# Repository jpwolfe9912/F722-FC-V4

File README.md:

# F722 Flight Controller V4
[Schematic.pdf](https://github.com/Jpwolfe9912/F722-FC-V4/files/6743878/Schematic.pdf)

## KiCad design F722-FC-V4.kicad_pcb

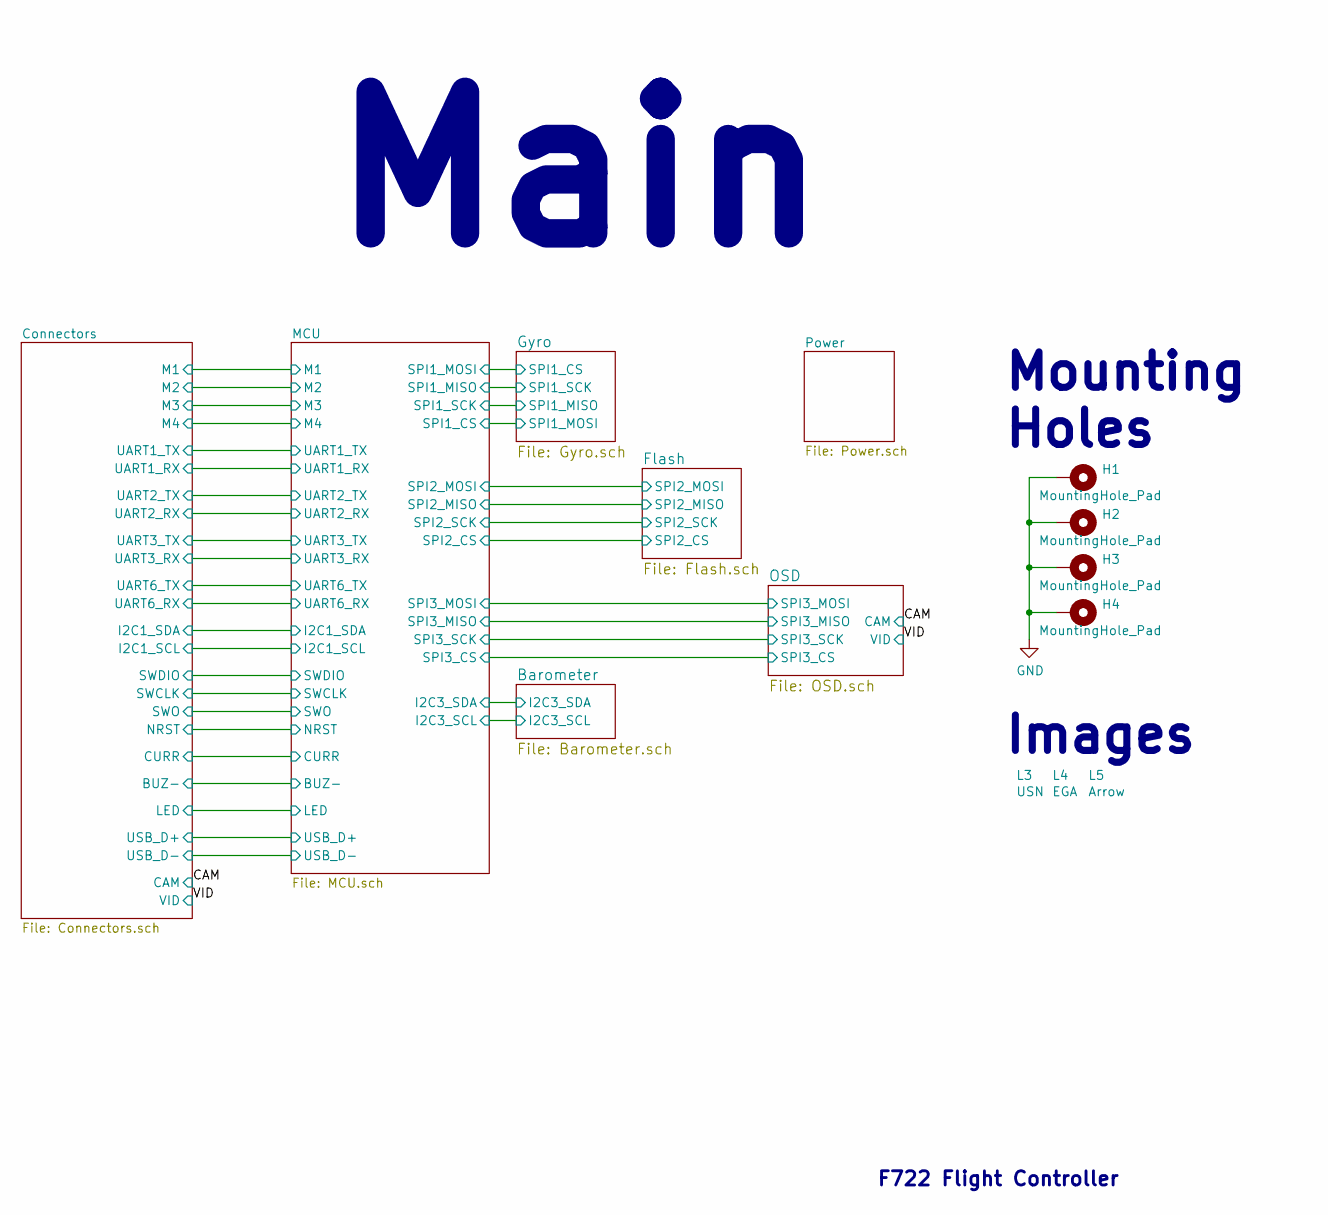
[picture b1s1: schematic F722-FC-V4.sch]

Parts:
H1, H2, H3, H4: MountingHole_Pad; MountingHole_2.7mm_Pad
L3: USN
L4: EGA
L5: Arrow

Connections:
GND: H1.1, H2.1, H3.1, H4.1; also elsewhere on the board

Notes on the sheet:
Mounting Holes
Images
Main
F722 Flight Controller

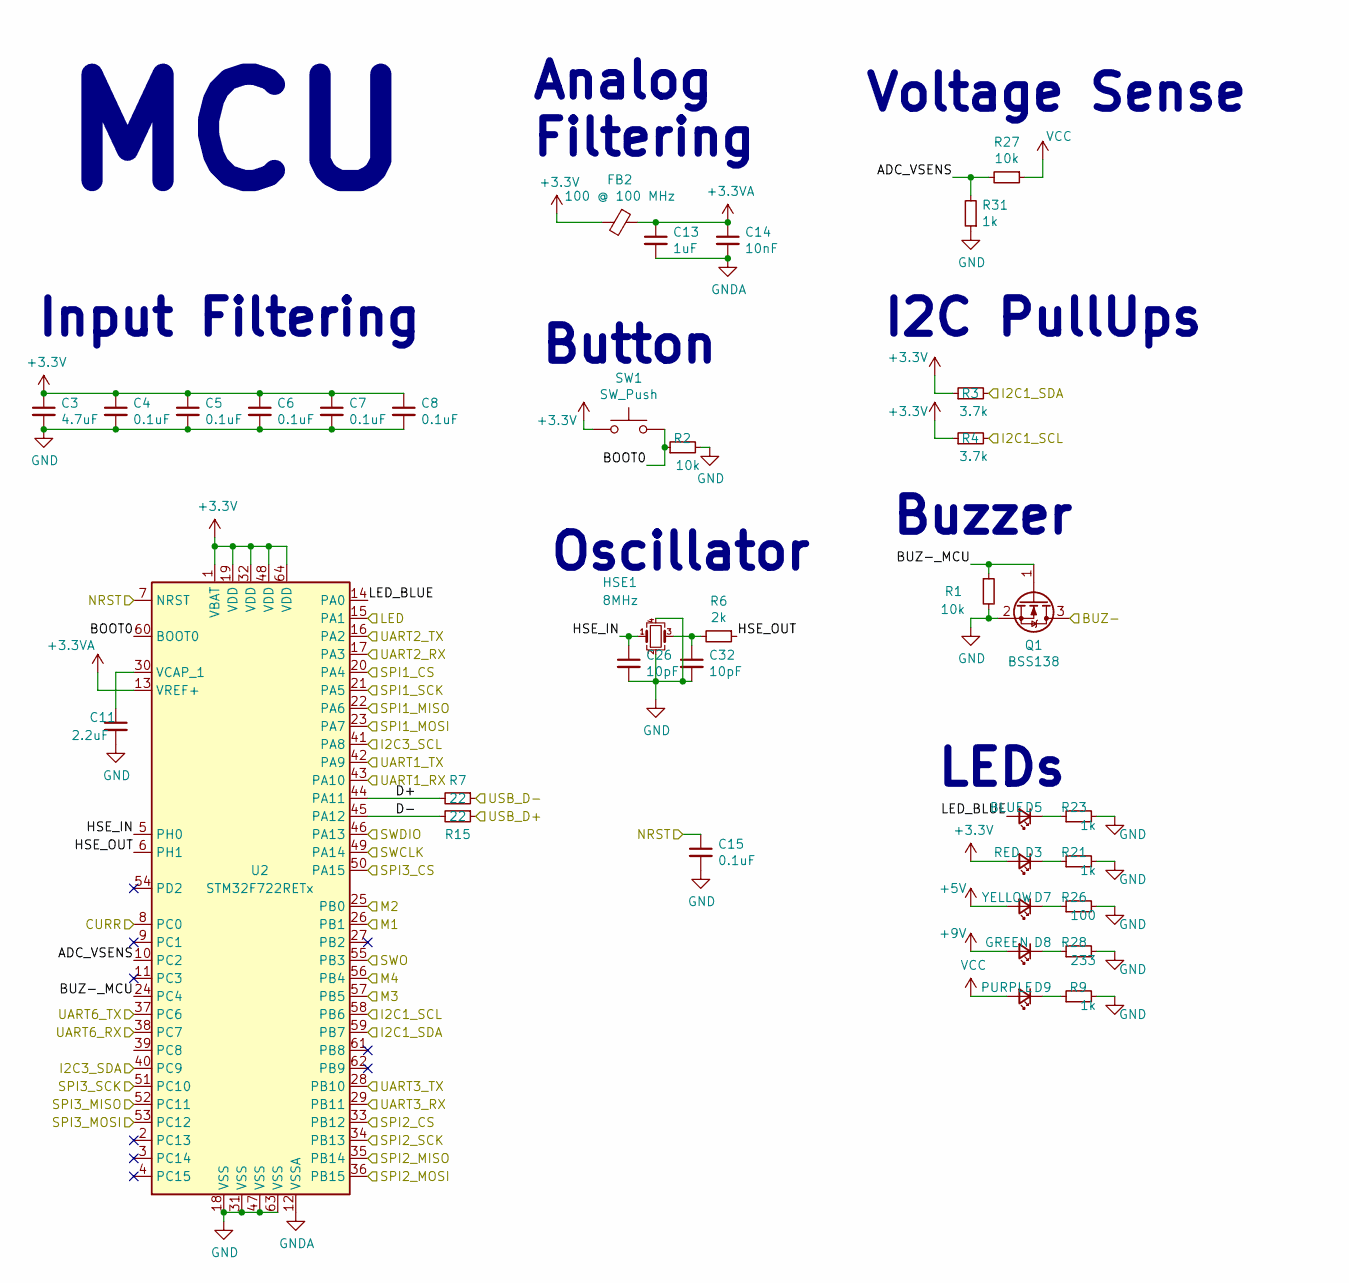
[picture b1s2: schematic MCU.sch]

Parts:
C3: 4.7uF; C_0402_1005Metric
C4, C5, C6, C7, C8, C15: 0.1uF; C_0402_1005Metric
C11: 2.2uF; C_0402_1005Metric
C13: 1uF; C_0402_1005Metric
C14: 10nF; C_0402_1005Metric
C26, C32: 10pF; C_0402_1005Metric
D3: RED; LED_0603_1608Metric
D5: BLUE; LED_0603_1608Metric
D7: YELLOW; LED_0603_1608Metric
D8: GREEN; LED_0603_1608Metric
D9: PURPLE; LED_0603_1608Metric
FB2: 100 @ 100 MHz; L_0603_1608Metric
HSE1: 8MHz; Oscillator_SMD_Abracon_ASE-4Pin_3.2x2.5mm
Q1: BSS138; SOT-23
R1, R2, R27: 10k; R_0402_1005Metric
R3, R4: 3.7k; R_0402_1005Metric
R6: 2k; R_0402_1005Metric
R7, R15: 22; R_0402_1005Metric
R9, R21, R23, R31: 1k; R_0402_1005Metric
R26: 100; R_0402_1005Metric
R28: 233; R_0402_1005Metric
SW1: SW_Push; SW_SPST_B3U-1000P
U2: STM32F722RETx; LQFP-64_10x10mm_P0.5mm

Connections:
+3.3VA: C13.1, C14.1, FB2.1, U2.13 (VREF+)
+5V: D7.2 (A); also elsewhere on the board
+9V: D8.2 (A); also elsewhere on the board
/Barometer/I2C3_SCL: U2.41 (PA8); also elsewhere on the board
/Barometer/I2C3_SDA: U2.40 (PC9); also elsewhere on the board
/Connectors/BUZ-: Q1.3 (D); also elsewhere on the board
/Connectors/CURR: U2.8 (PC0); also elsewhere on the board
/Connectors/I2C1_SCL: R4.2, U2.58 (PB6); also elsewhere on the board
/Connectors/I2C1_SDA: R3.2, U2.59 (PB7); also elsewhere on the board
/Connectors/LED: U2.15 (PA1); also elsewhere on the board
/Connectors/M1: U2.26 (PB1); also elsewhere on the board
/Connectors/M2: U2.25 (PB0); also elsewhere on the board
/Connectors/M3: U2.57 (PB5); also elsewhere on the board
/Connectors/M4: U2.56 (PB4); also elsewhere on the board
/Connectors/SWCLK: U2.49 (PA14); also elsewhere on the board
/Connectors/SWDIO: U2.46 (PA13); also elsewhere on the board
/Connectors/SWO: U2.55 (PB3); also elsewhere on the board
/Connectors/UART1_RX: U2.43 (PA10); also elsewhere on the board
/Connectors/UART1_TX: U2.42 (PA9); also elsewhere on the board
/Connectors/UART2_RX: U2.17 (PA3); also elsewhere on the board
/Connectors/UART2_TX: U2.16 (PA2); also elsewhere on the board
/Connectors/UART3_RX: U2.29 (PB11); also elsewhere on the board
/Connectors/UART3_TX: U2.28 (PB10); also elsewhere on the board
/Connectors/UART6_RX: U2.38 (PC7); also elsewhere on the board
/Connectors/UART6_TX: U2.37 (PC6); also elsewhere on the board
/Connectors/USB_D+: R15.1; also elsewhere on the board
/Connectors/USB_D-: R7.1; also elsewhere on the board
/Flash/SPI2_CS: U2.33 (PB12); also elsewhere on the board
/Flash/SPI2_MISO: U2.35 (PB14); also elsewhere on the board
/Flash/SPI2_MOSI: U2.36 (PB15); also elsewhere on the board
/Flash/SPI2_SCK: U2.34 (PB13); also elsewhere on the board
/Gyro/SPI1_CS: U2.23 (PA7); also elsewhere on the board
/Gyro/SPI1_MISO: U2.21 (PA5); also elsewhere on the board
/MCU/ADC_VSENS: R27.2, R31.2, U2.10 (PC2)
/MCU/BOOT0: R2.1, SW1.2, U2.60 (BOOT0)
/MCU/BUZ-_MCU: Q1.1 (G), R1.1, U2.24 (PC4)
/MCU/D+: R7.2, U2.44 (PA11)
/MCU/D-: R15.2, U2.45 (PA12)
/MCU/HSE_IN: C26.1, HSE1.1, U2.5 (PH0)
/MCU/HSE_OUT: R6.1, U2.6 (PH1)
/MCU/LED_BLUE: D5.2 (A), U2.14 (PA0)
/MCU/NRST: C15.1, U2.7 (NRST)
/MCU/SPI1_CS: U2.20 (PA4); also elsewhere on the board
/MCU/SPI1_MISO: U2.22 (PA6); also elsewhere on the board
/MCU/SPI3_CS: U2.50 (PA15); also elsewhere on the board
/MCU/SPI3_MISO: U2.52 (PC11); also elsewhere on the board
/MCU/SPI3_MOSI: U2.53 (PC12); also elsewhere on the board
/MCU/SPI3_SCK: U2.51 (PC10); also elsewhere on the board
GND: C3.2, C4.2, C5.2, C6.2, C7.2, C8.2, C11.2, C15.2, C26.2, C32.2, HSE1.2, HSE1.4, Q1.2 (S), R1.2, R2.2, R9.2, R21.2, R23.2, R26.2, R28.2, R31.1, U2.18 (VSS), U2.31 (VSS), U2.47 (VSS), U2.63 (VSS); also elsewhere on the board
GNDA: C13.2, C14.2, U2.12 (VSSA)
unnamed: C11.1, U2.30 (VCAP_1)
unnamed: C32.1, HSE1.3, R6.2
unnamed: D3.1 (K), R21.1
unnamed: D5.1 (K), R23.1
unnamed: D7.1 (K), R26.1
unnamed: D8.1 (K), R28.1
unnamed: D9.1 (K), R9.1
VCC: D9.2 (A), R27.1; also elsewhere on the board

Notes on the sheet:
LEDs
Buzzer
I2C PullUps
Voltage Sense
Analog Filtering
Input Filtering
Button
Oscillator
MCU

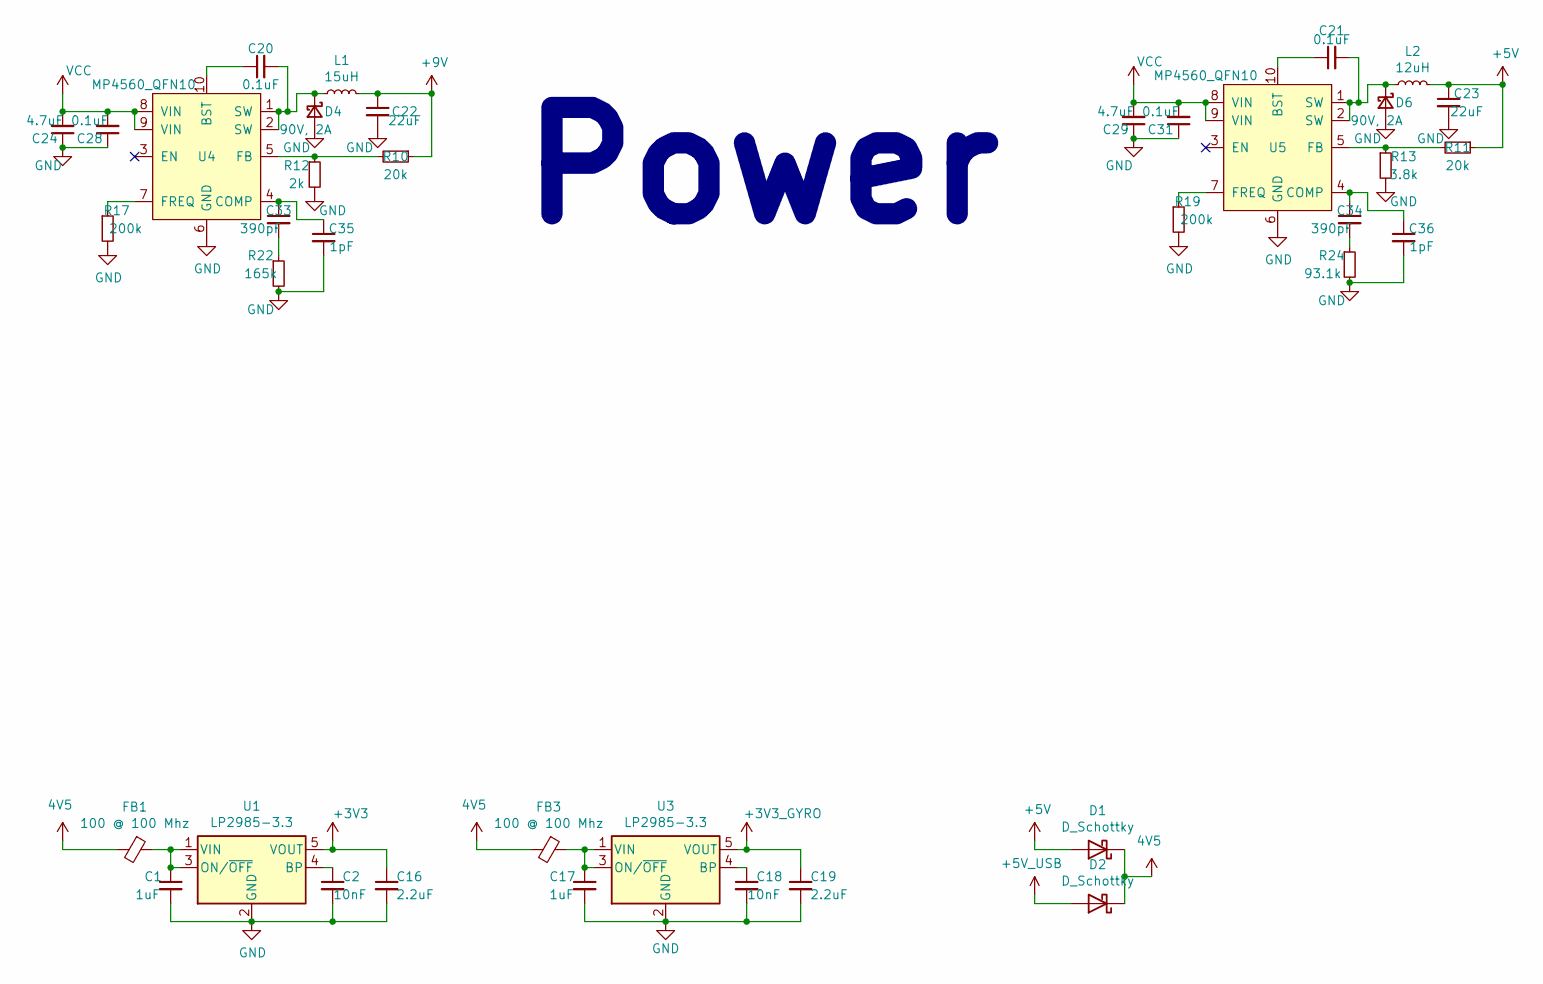
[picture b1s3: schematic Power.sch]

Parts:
C1, C17: 1uF; C_0402_1005Metric
C2, C18: 10nF; C_0402_1005Metric
C16, C19: 2.2uF; C_0402_1005Metric
C20, C21, C28, C31: 0.1uF; C_0402_1005Metric
C22, C23: 22uF; C_0603_1608Metric
C24, C29: 4.7uF; C_0603_1608Metric
C33, C34: 390pF; C_0402_1005Metric
C35, C36: 1pF; C_0402_1005Metric
D1, D2: D_Schottky; SBR3U30P1-7
D4, D6: 90V, 2A; D_SOD-123F
FB1, FB3: 100 @ 100 Mhz; L_0603_1608Metric
L1: 15uH; L_Bourns-SRN3015
L2: 12uH; L_Bourns-SRN3015
R10, R11: 20k; R_0402_1005Metric
R12: 2k; R_0402_1005Metric
R13: 3.8k; R_0402_1005Metric
R17, R19: 200k; R_0402_1005Metric
R22: 165k; R_0402_1005Metric
R24: 93.1k; R_0402_1005Metric
U1, U3: LP2985-3.3; SOT-23-5
U4, U5: MP4560_QFN10; DFN-10-1EP_3x3mm_P0.5mm_EP1.7x2.5mm

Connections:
4V5: D1.1 (K), D2.1 (K), FB1.2, FB3.2; also elsewhere on the board
+3V3_GYRO: C19.1, U3.5 (VOUT); also elsewhere on the board
+5V: C23.1, D1.2 (A), L2.2, R11.1; also elsewhere on the board
+5V_USB: D2.2 (A); also elsewhere on the board
+9V: C22.1, L1.2, R10.1; also elsewhere on the board
GND: C1.2, C2.2, C16.2, C17.2, C18.2, C19.2, C22.2, C23.2, C24.1, C28.1, C29.1, C31.1, C35.2, C36.2, D4.2 (A), D6.2 (A), R12.2, R13.2, R17.2, R19.2, R22.2, R24.2, U1.2 (GND), U3.2 (GND), U4.6 (GND), U5.6 (GND); also elsewhere on the board
unnamed: C1.1, FB1.1, U1.1 (VIN), U1.3 (ON/~OFF~)
unnamed: C2.1, U1.4 (BP)
unnamed: C17.1, FB3.1, U3.1 (VIN), U3.3 (ON/~OFF~)
unnamed: C18.1, U3.4 (BP)
unnamed: C20.1, U4.10 (BST)
unnamed: C20.2, D4.1 (K), L1.1, U4.1 (SW), U4.2 (SW)
unnamed: C21.1, U5.10 (BST)
unnamed: C21.2, D6.1 (K), L2.1, U5.1 (SW), U5.2 (SW)
unnamed: C33.1, C35.1, U4.4 (COMP)
unnamed: C33.2, R22.1
unnamed: C34.1, C36.1, U5.4 (COMP)
unnamed: C34.2, R24.1
unnamed: R10.2, R12.1, U4.5 (FB)
unnamed: R11.2, R13.1, U5.5 (FB)
unnamed: R17.1, U4.7 (FREQ)
unnamed: R19.1, U5.7 (FREQ)
VCC: C24.2, C28.2, C29.2, C31.2, U4.8 (VIN), U4.9 (VIN), U5.8 (VIN), U5.9 (VIN); also elsewhere on the board

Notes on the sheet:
Power

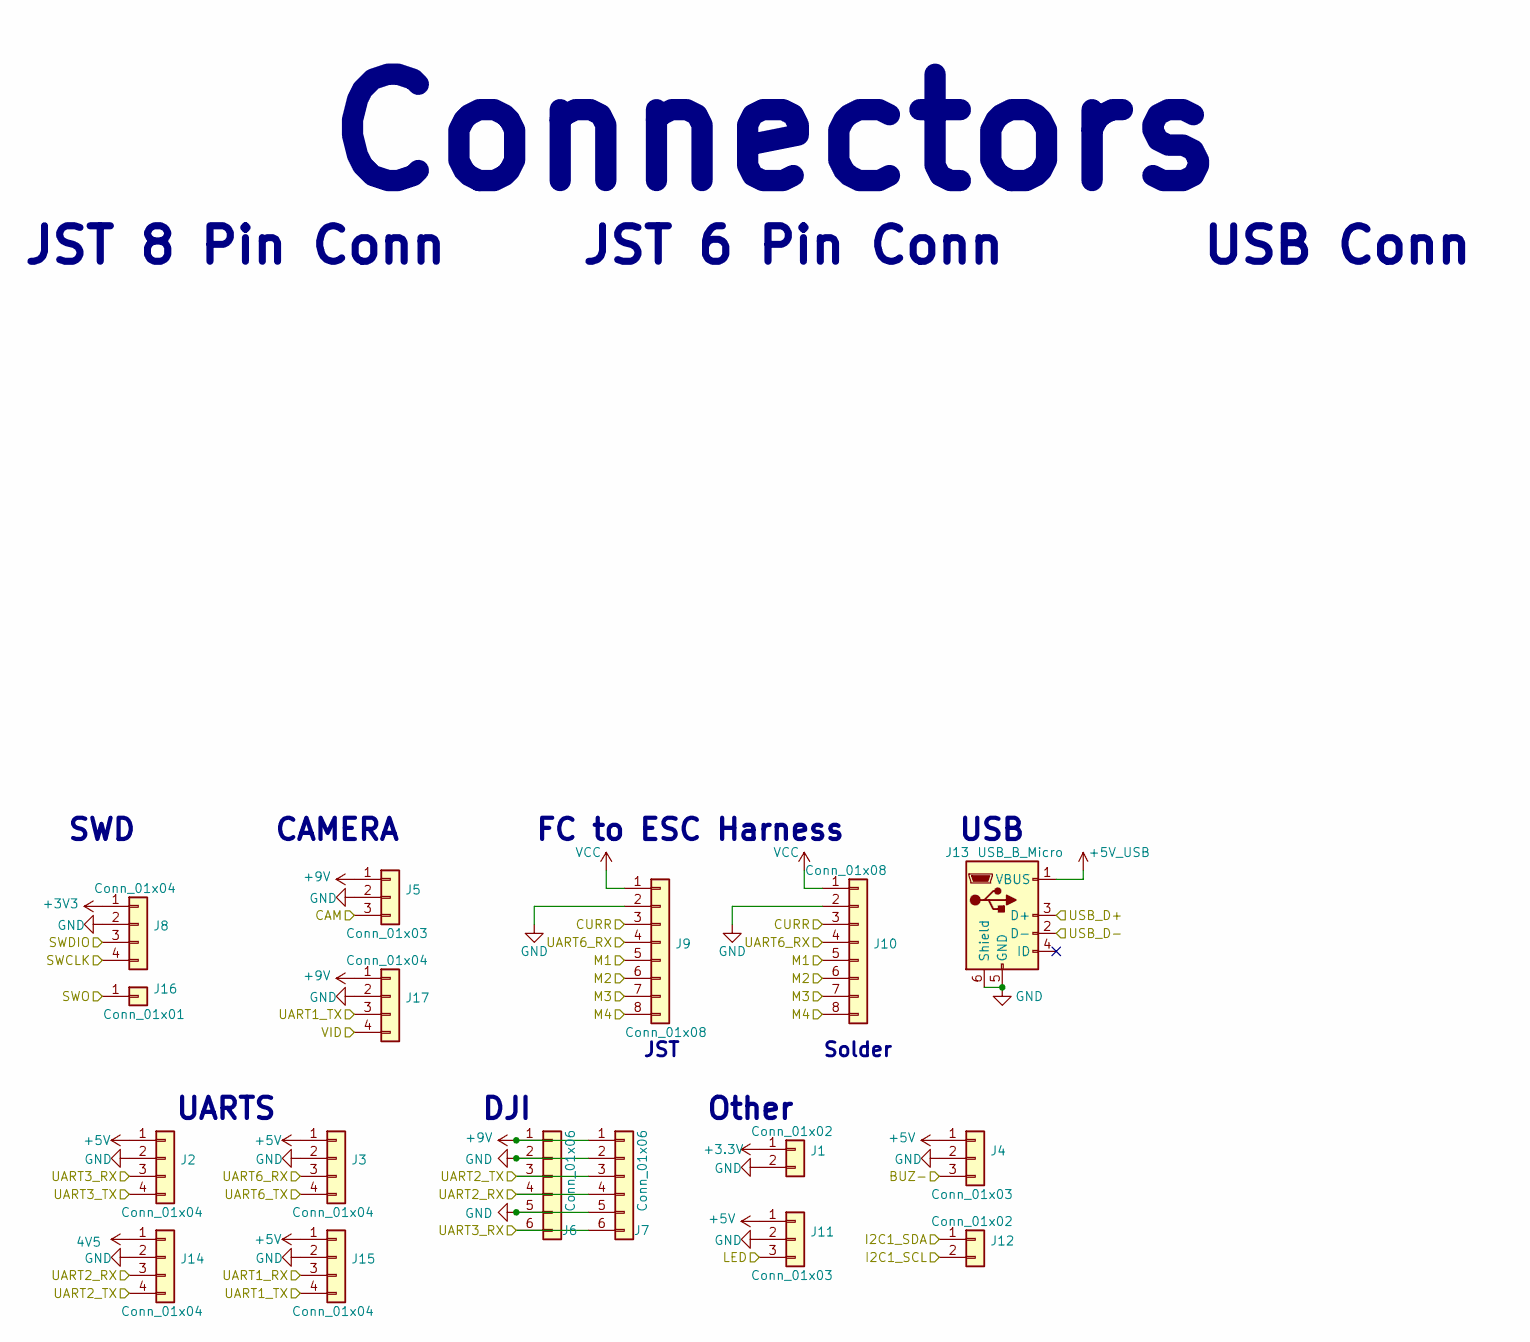
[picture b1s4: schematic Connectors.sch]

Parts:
J1, J12: Conn_01x02; SolderWire-0.1sqmm_1x02_P3.6mm_D0.4mm_OD1mm
J2, J3, J14, J15, J17: Conn_01x04; SolderWire-0.1sqmm_1x04_P3.6mm_D0.4mm_OD1mm
J4, J5, J11: Conn_01x03; SolderWire-0.1sqmm_1x03_P3.6mm_D0.4mm_OD1mm
J6: Conn_01x06; JST_SM06B-SRSS-TB(LF)(SN)
J7: Conn_01x06; Connector_Wire_Solder_DJI
J8: Conn_01x04; PinHeader_1x04_P2.54mm_Vertical
J9: Conn_01x08; JST_SH_SM08B-SRSS-TB_1x08-1MP_P1.00mm_Horizontal
J10: Conn_01x08; SolderWire-0.1sqmm_1x08_D0.4mm_OD1mm
J13: USB_B_Micro; USB_Micro-B_Amphenol_10103594-0001LF_Horizontal
J16: Conn_01x01; SolderWire-0.1sqmm_1x01_D0.4mm_OD1mm

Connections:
4V5: J14.1; also elsewhere on the board
+5V: J2.1, J3.1, J4.1, J11.1, J15.1; also elsewhere on the board
+5V_USB: J13.1 (VBUS); also elsewhere on the board
+9V: J5.1, J6.1, J7.1, J17.1; also elsewhere on the board
/CAM: J5.3; also elsewhere on the board
/Connectors/BUZ-: J4.3; also elsewhere on the board
/Connectors/CURR: J9.3, J10.3; also elsewhere on the board
/Connectors/I2C1_SCL: J12.2; also elsewhere on the board
/Connectors/I2C1_SDA: J12.1; also elsewhere on the board
/Connectors/LED: J11.3; also elsewhere on the board
/Connectors/M1: J9.5, J10.5; also elsewhere on the board
/Connectors/M2: J9.6, J10.6; also elsewhere on the board
/Connectors/M3: J9.7, J10.7; also elsewhere on the board
/Connectors/M4: J9.8, J10.8; also elsewhere on the board
/Connectors/SWCLK: J8.4; also elsewhere on the board
/Connectors/SWDIO: J8.3; also elsewhere on the board
/Connectors/SWO: J16.1; also elsewhere on the board
/Connectors/UART1_RX: J15.3; also elsewhere on the board
/Connectors/UART1_TX: J15.4, J17.3; also elsewhere on the board
/Connectors/UART2_RX: J6.4, J7.4, J14.3; also elsewhere on the board
/Connectors/UART2_TX: J6.3, J7.3, J14.4; also elsewhere on the board
/Connectors/UART3_RX: J2.3, J6.6, J7.6; also elsewhere on the board
/Connectors/UART3_TX: J2.4; also elsewhere on the board
/Connectors/UART6_RX: J3.3, J9.4, J10.4; also elsewhere on the board
/Connectors/UART6_TX: J3.4; also elsewhere on the board
/Connectors/USB_D+: J13.3 (D+); also elsewhere on the board
/Connectors/USB_D-: J13.2 (D-); also elsewhere on the board
/VID: J17.4; also elsewhere on the board
GND: J1.2, J2.2, J3.2, J4.2, J5.2, J6.2, J6.5, J7.2, J7.5, J8.2, J9.2, J10.2, J11.2, J13.5 (GND), J13.6 (Shield), J14.2, J15.2, J17.2; also elsewhere on the board
VCC: J9.1, J10.1; also elsewhere on the board

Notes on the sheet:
FC to ESC Harness
UARTS
CAMERA
DJI
SWD
Other
JST
Solder
USB
JST 8 Pin Conn
JST 6 Pin Conn
USB Conn
Connectors

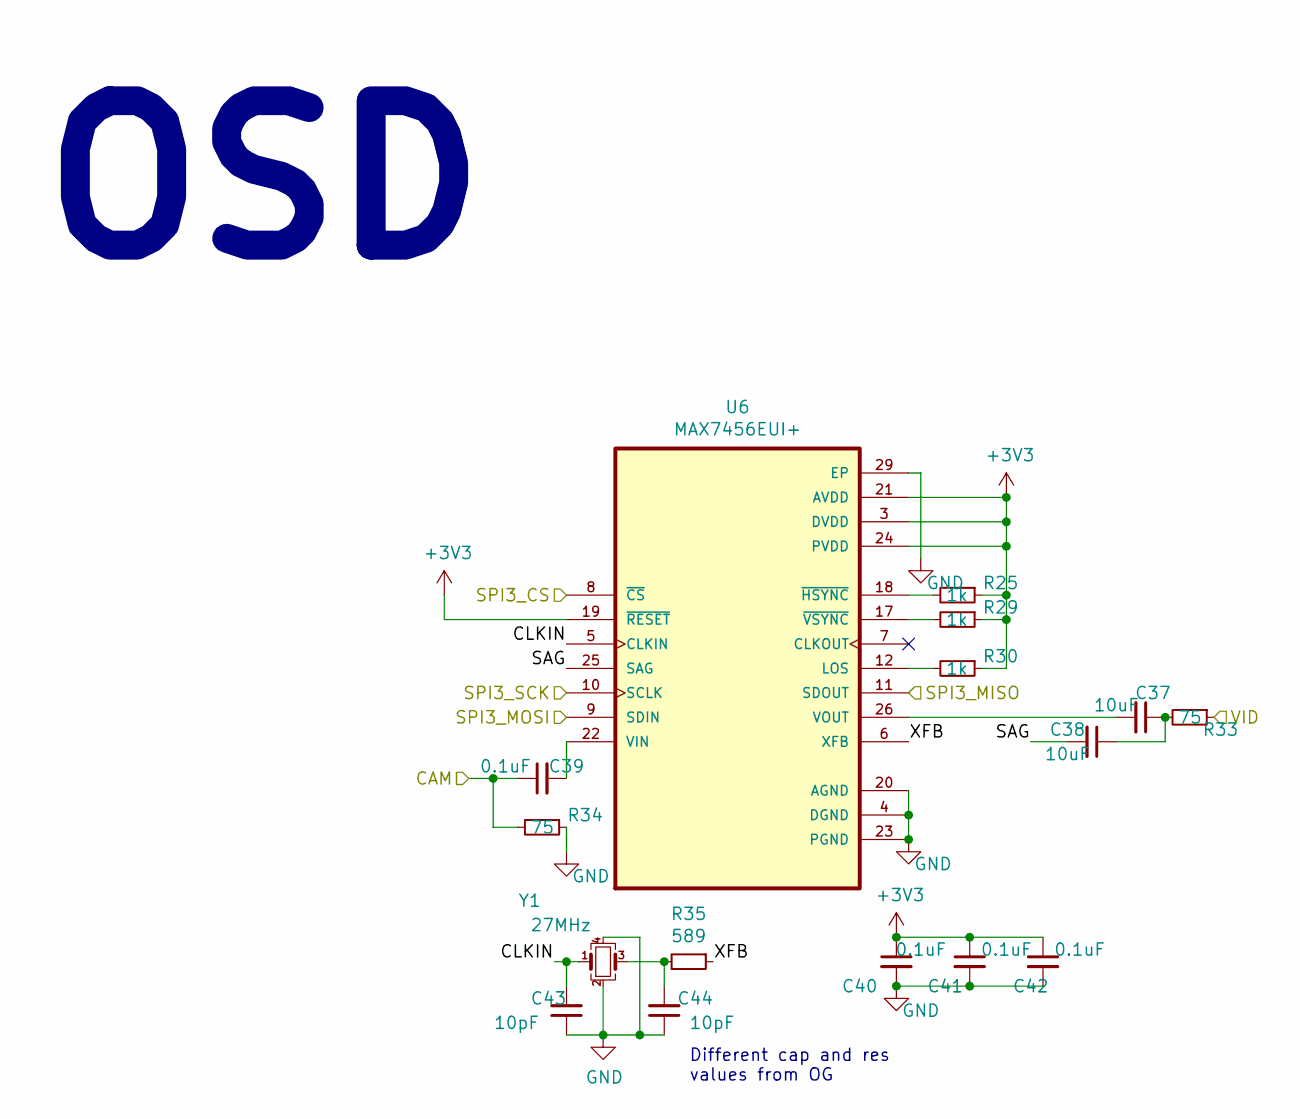
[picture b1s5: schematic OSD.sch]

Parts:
C37, C38: 10uF; C_0402_1005Metric
C39, C40, C41, C42: 0.1uF; C_0402_1005Metric
C43, C44: 10pF; C_0402_1005Metric
R25, R29, R30: 1k; R_0402_1005Metric
R33, R34: 75; R_0402_1005Metric
R35: 589; R_0402_1005Metric
U6: MAX7456EUI+; MAX7456EUI&plus_T
Y1: 27MHz; Oscillator_SMD_Abracon_ASE-4Pin_3.2x2.5mm

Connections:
/CAM: C39.1, R34.2; also elsewhere on the board
/MCU/SPI3_CS: U6.8 (~CS); also elsewhere on the board
/MCU/SPI3_MISO: U6.11 (SDOUT); also elsewhere on the board
/MCU/SPI3_MOSI: U6.9 (SDIN); also elsewhere on the board
/MCU/SPI3_SCK: U6.10 (SCLK); also elsewhere on the board
/OSD/CLKIN: C43.2, U6.5 (CLKIN), Y1.1
/OSD/SAG: C38.2, U6.25 (SAG)
/OSD/XFB: R35.1, U6.6 (XFB)
/VID: R33.1; also elsewhere on the board
GND: C40.2, C41.2, C42.2, C43.1, C44.1, R34.1, U6.4 (DGND), U6.20 (AGND), U6.23 (PGND), U6.29 (EP), Y1.2, Y1.4; also elsewhere on the board
unnamed: C37.1, C38.1, R33.2
unnamed: C37.2, U6.26 (VOUT)
unnamed: C39.2, U6.22 (VIN)
unnamed: C44.2, R35.2, Y1.3
unnamed: R25.2, U6.18 (~HSYNC)
unnamed: R29.2, U6.17 (~VSYNC)
unnamed: R30.2, U6.12 (LOS)

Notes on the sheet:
Different cap and res values from OG
OSD

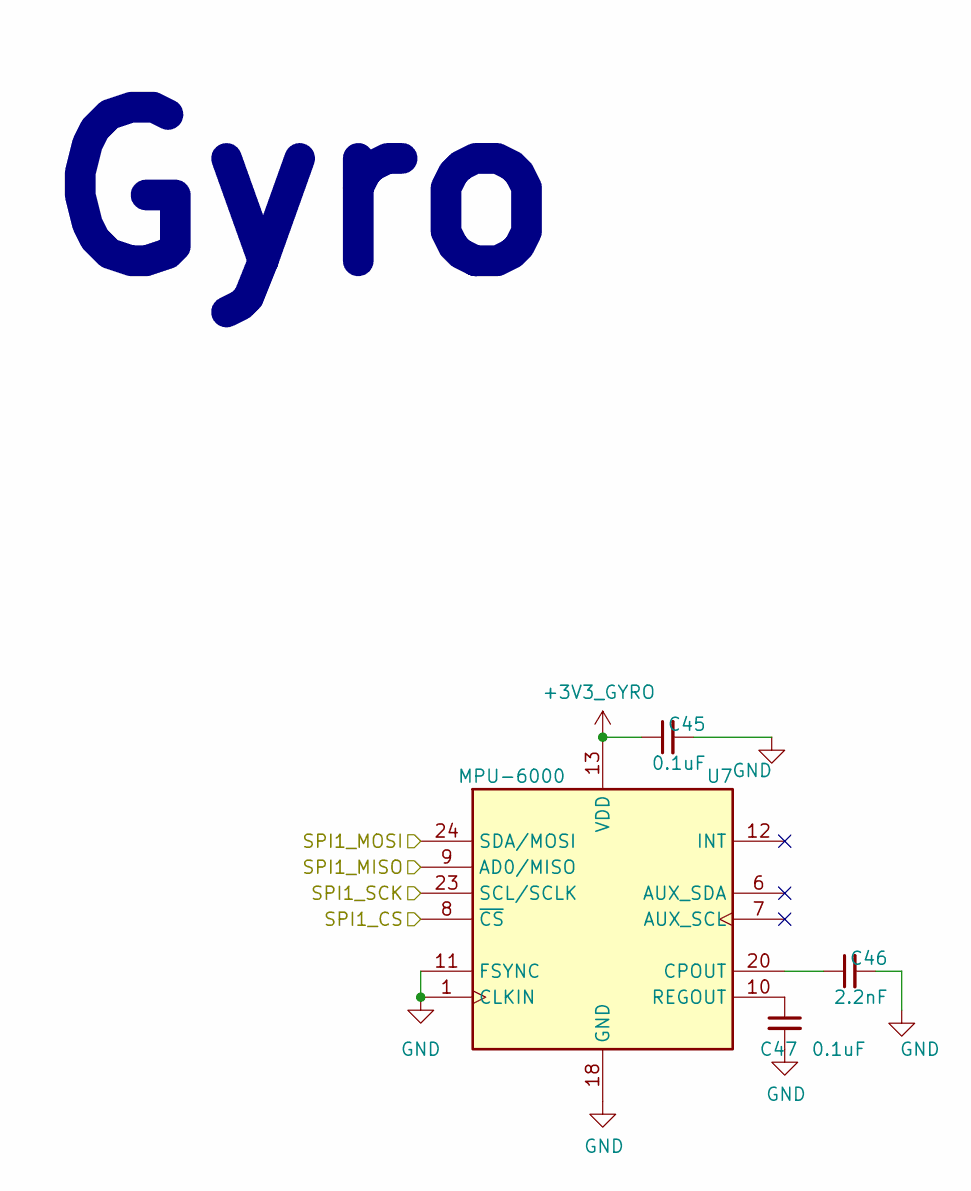
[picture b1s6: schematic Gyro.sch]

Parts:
C45, C47: 0.1uF; C_0402_1005Metric
C46: 2.2nF; C_0402_1005Metric
U7: MPU-6000; InvenSense_QFN-24_4x4mm_P0.5mm

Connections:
+3V3_GYRO: C45.1, U7.13 (VDD); also elsewhere on the board
/Gyro/SPI1_CS: U7.8 (~CS); also elsewhere on the board
/Gyro/SPI1_MISO: U7.9 (AD0/MISO); also elsewhere on the board
/MCU/SPI1_CS: U7.24 (SDA/MOSI); also elsewhere on the board
/MCU/SPI1_MISO: U7.23 (SCL/SCLK); also elsewhere on the board
GND: C45.2, C46.2, C47.2, U7.1 (CLKIN), U7.11 (FSYNC), U7.18 (GND); also elsewhere on the board
unnamed: C46.1, U7.20 (CPOUT)
unnamed: C47.1, U7.10 (REGOUT)

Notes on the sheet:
Gyro

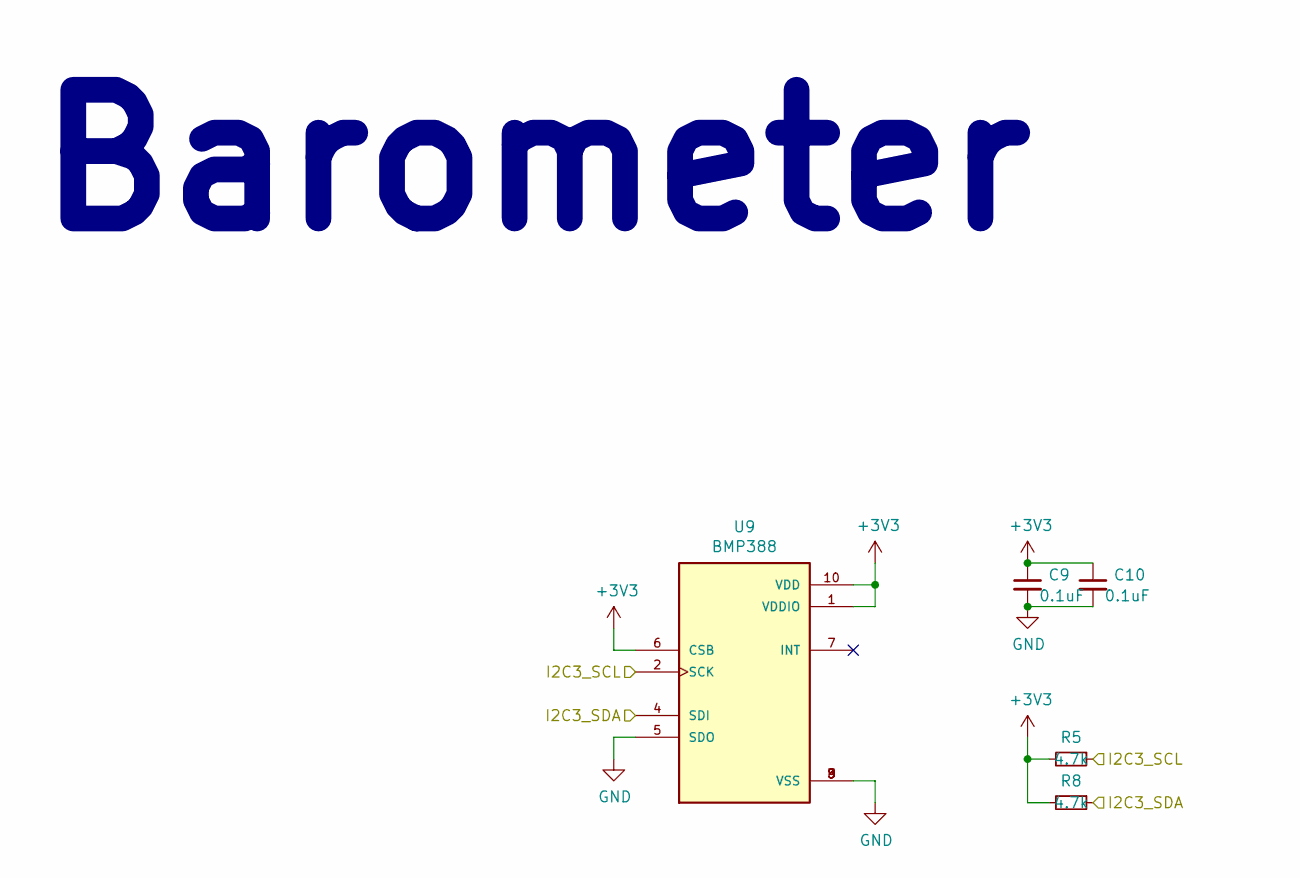
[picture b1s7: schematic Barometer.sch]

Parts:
C9, C10: 0.1uF; C_0402_1005Metric
R5, R8: 4.7k; R_0402_1005Metric
U9: BMP388

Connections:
/Barometer/I2C3_SCL: R5.1, U9.2 (SCK); also elsewhere on the board
/Barometer/I2C3_SDA: R8.1, U9.4 (SDI); also elsewhere on the board
GND: C9.2, C10.2, U9.3 (VSS), U9.5 (SDO), U9.8 (VSS), U9.9 (VSS); also elsewhere on the board

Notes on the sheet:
Barometer

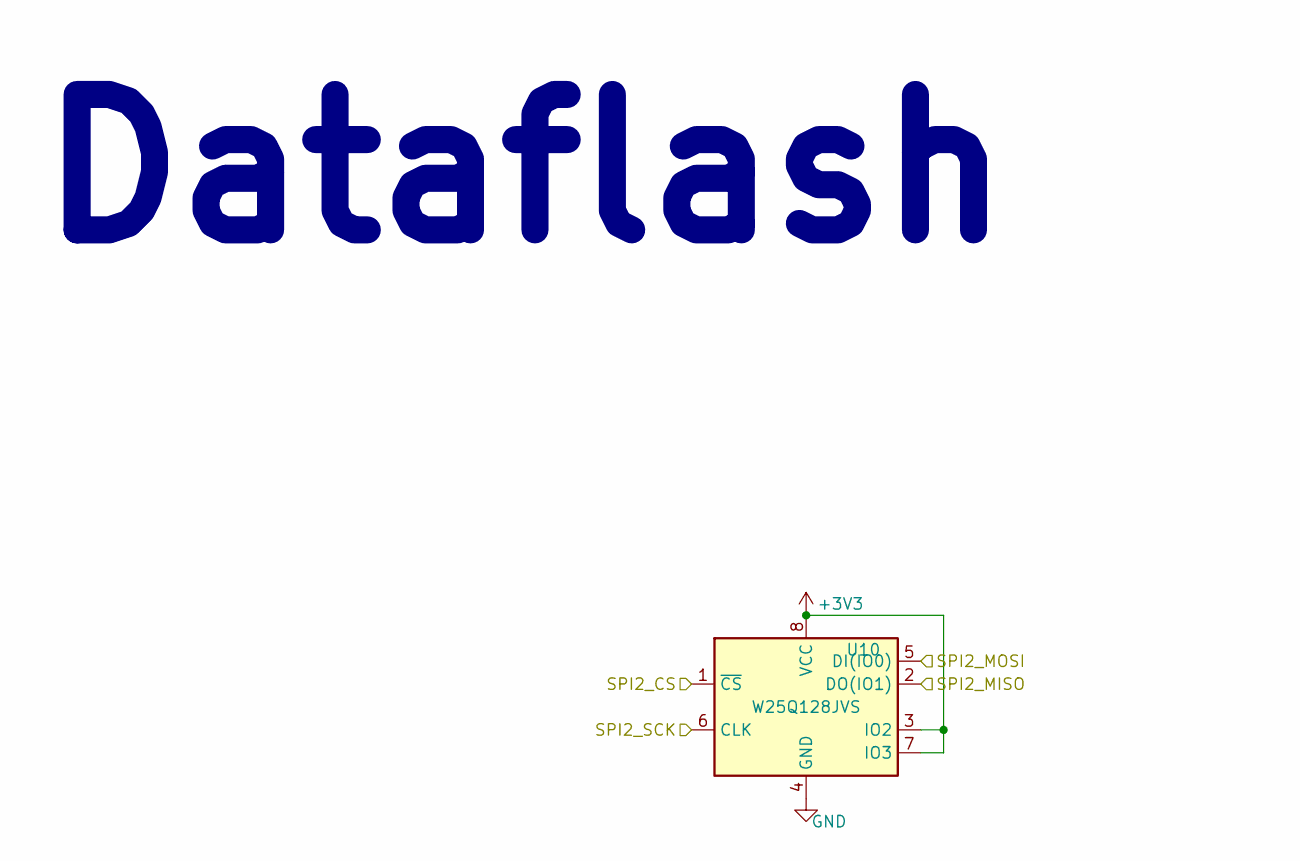
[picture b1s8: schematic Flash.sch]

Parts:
U10: W25Q128JVS; SOIC-8_5.23x5.23mm_P1.27mm

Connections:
/Flash/SPI2_CS: U10.1 (~CS); also elsewhere on the board
/Flash/SPI2_MISO: U10.2 (DO(IO1)); also elsewhere on the board
/Flash/SPI2_MOSI: U10.5 (DI(IO0)); also elsewhere on the board
/Flash/SPI2_SCK: U10.6 (CLK); also elsewhere on the board
GND: U10.4 (GND); also elsewhere on the board

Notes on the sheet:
Dataflash

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
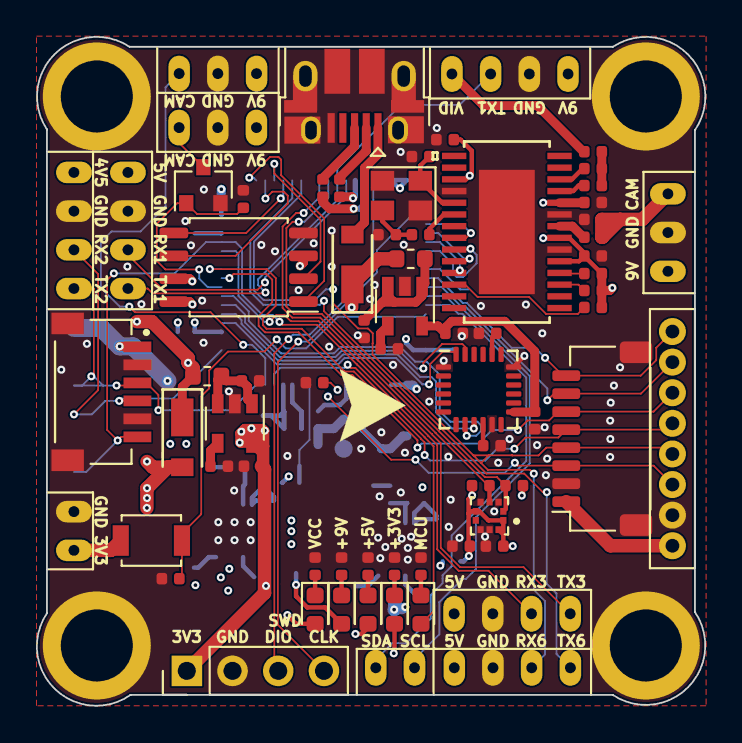
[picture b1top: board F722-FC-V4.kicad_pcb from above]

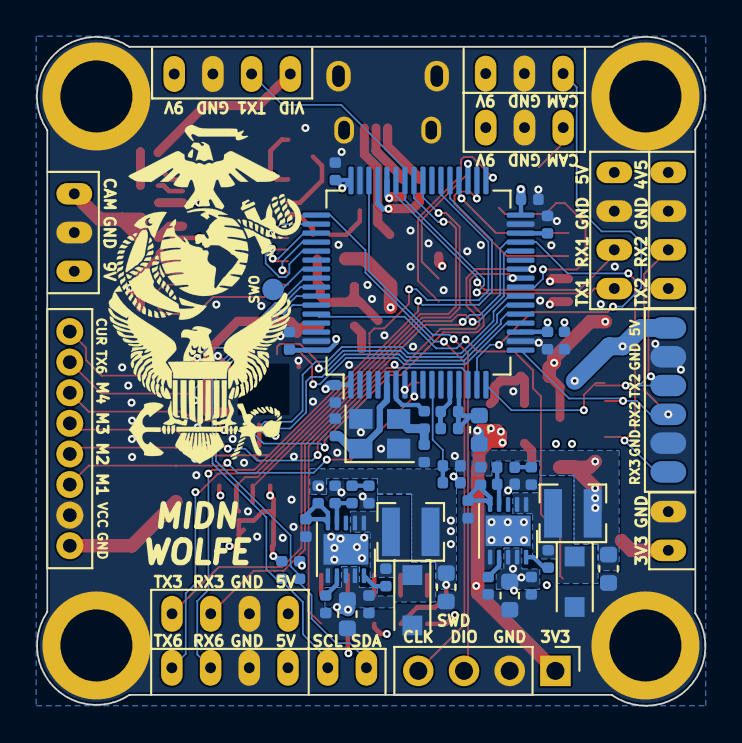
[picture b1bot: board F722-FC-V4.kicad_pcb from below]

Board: 4 copper layers, 37.1 x 37.2 mm, 124 parts (49 on the bottom side), 92 nets.

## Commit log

2021-06-17 Added all new files
2021-06-18 Updated the schematics to include pictures
2021-06-18 Rerouted a bit
2021-06-30 Changed around routing
2021-06-30 Added teardrops
2021-06-30 Added PNGs
2021-07-04 Unknown changes
